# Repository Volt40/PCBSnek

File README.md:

# PCBSnek
PCB Business card with an integrated playable snake game.
Files are ready to be manufactured and assembled with JLCPCB.

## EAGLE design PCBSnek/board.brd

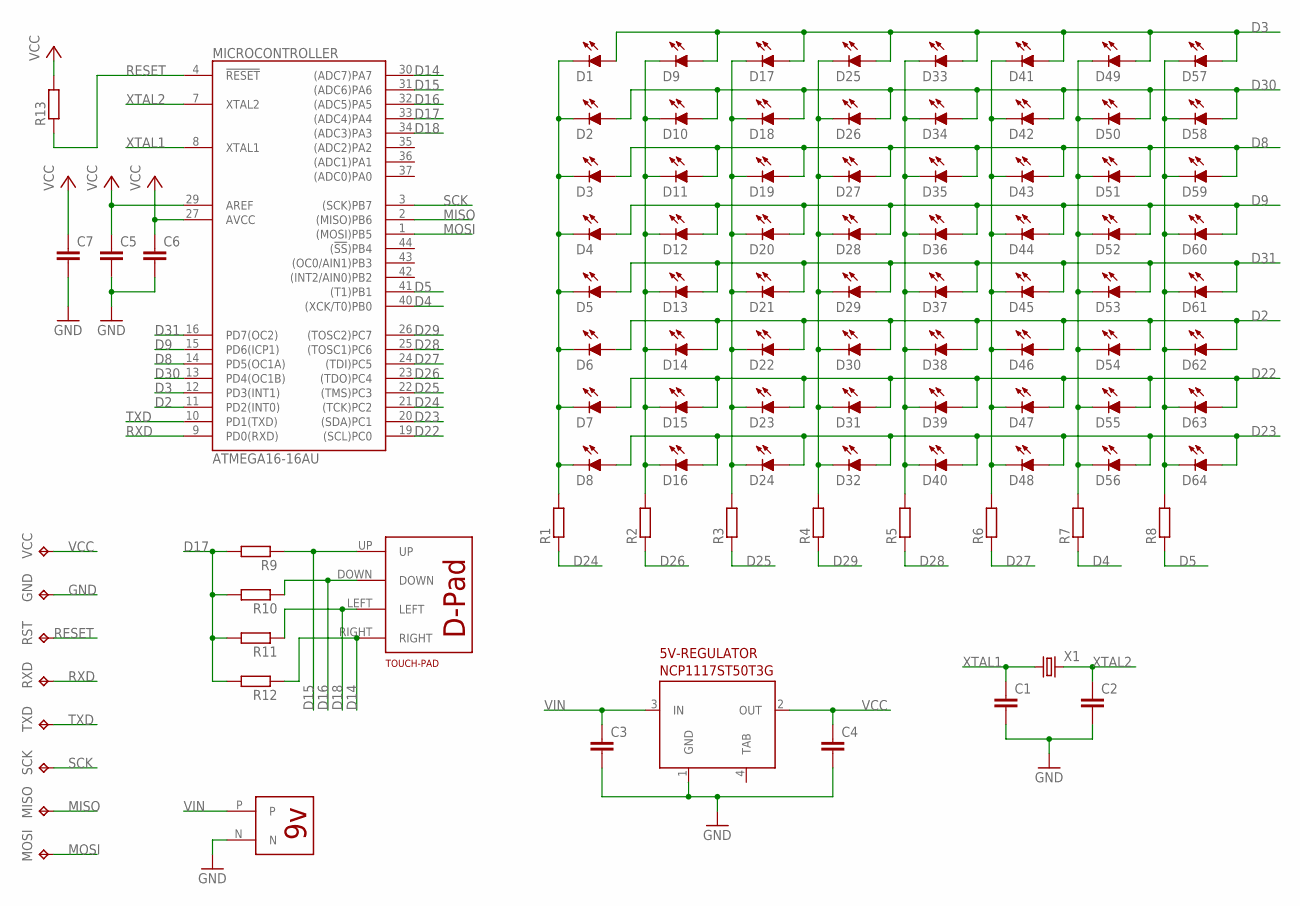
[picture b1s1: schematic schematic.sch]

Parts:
5V-REGULATOR: NCP1117ST50T3G; SOT223
C1, C2, C3, C4, C5, C6, C7: C-EUC0603; C0603
D1, D2, D3, D4, D5, D6, D7, D8, D9, D10, D11, D12, D13, D14, D15, D16, D17, D18, D19, D20, D21, D22, D23, D24, D25, D26, D27, D28, D29, D30, D31, D32, D33, D34, D35, D36, D37, D38, D39, D40, D41, D42, D43, D44, D45, D46, D47, D48, D49, D50, D51, D52, D53, D54, D55, D56, D57, D58, D59, D60, D61, D62, D63, D64: LED_LEDCHIP-LED0603MP; LED_CHIP-LED0603MP
GND: TPB2,54; B2,54
MICROCONTROLLER: ATMEGA16-16AU; QFP44_10X10_0.80
MISO: TPB2,54; B2,54
MOSI: TPB2,54; B2,54
R1, R2, R3, R4, R5, R6, R7, R8, R9, R10, R11, R12, R13: R-EU_R0603; R0603
RST: TPB2,54; B2,54
RXD: TPB2,54; B2,54
SCK: TPB2,54; B2,54
TOUCH-PAD: DPAD; D-PAD
TXD: TPB2,54; B2,54
U$1: BAT
VCC: TPB2,54; B2,54
X1: X322516MLB4SI; SMD3225

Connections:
D2: D6.A, D14.A, D22.A, D30.A, D38.A, D46.A, D54.A, D62.A, MICROCONTROLLER.11 (PD2(INT0))
D3: D1.A, D9.A, D17.A, D25.A, D33.A, D41.A, D49.A, D57.A, MICROCONTROLLER.12 (PD3(INT1))
D4: MICROCONTROLLER.40 ((XCK/T0)PB0), R7.1
D5: MICROCONTROLLER.41 ((T1)PB1), R8.1
D8: D3.A, D11.A, D19.A, D27.A, D35.A, D43.A, D51.A, D59.A, MICROCONTROLLER.14 (PD5(OC1A))
D9: D4.A, D12.A, D20.A, D28.A, D36.A, D44.A, D52.A, D60.A, MICROCONTROLLER.15 (PD6(ICP1))
D14: MICROCONTROLLER.30 ((ADC7)PA7), R12.1, TOUCH-PAD.RIGHT
D15: MICROCONTROLLER.31 ((ADC6)PA6), R9.1, TOUCH-PAD.UP
D16: MICROCONTROLLER.32 ((ADC5)PA5), R10.1, TOUCH-PAD.DOWN
D17: MICROCONTROLLER.33 ((ADC4)PA4), R9.2, R10.2, R11.2, R12.2
D18: MICROCONTROLLER.34 ((ADC3)PA3), R11.1, TOUCH-PAD.LEFT
D22: D7.A, D15.A, D23.A, D31.A, D39.A, D47.A, D55.A, D63.A, MICROCONTROLLER.19 ((SCL)PC0)
D23: D8.A, D16.A, D24.A, D32.A, D40.A, D48.A, D56.A, D64.A, MICROCONTROLLER.20 ((SDA)PC1)
D24: MICROCONTROLLER.21 ((TCK)PC2), R1.1
D25: MICROCONTROLLER.22 ((TMS)PC3), R3.1
D26: MICROCONTROLLER.23 ((TDO)PC4), R2.1
D27: MICROCONTROLLER.24 ((TDI)PC5), R6.1
D28: MICROCONTROLLER.25 ((TOSC1)PC6), R5.1
D29: MICROCONTROLLER.26 ((TOSC2)PC7), R4.1
D30: D2.A, D10.A, D18.A, D26.A, D34.A, D42.A, D50.A, D58.A, MICROCONTROLLER.13 (PD4(OC1B))
D31: D5.A, D13.A, D21.A, D29.A, D37.A, D45.A, D53.A, D61.A, MICROCONTROLLER.16 (PD7(OC2))
GND: 5V-REGULATOR.1 (GND), C1.2, C2.2, C3.2, C4.2, C5.2, C6.2, C7.2, GND.TP, MICROCONTROLLER.6 (GND), MICROCONTROLLER.18 (GND), MICROCONTROLLER.28 (GND), MICROCONTROLLER.39 (GND), U$1.N
MISO: MICROCONTROLLER.2 ((MISO)PB6), MISO.TP
MOSI: MICROCONTROLLER.1 ((MOSI)PB5), MOSI.TP
unnamed: D1.C, D2.C, D3.C, D4.C, D5.C, D6.C, D7.C, D8.C, R1.2
unnamed: D9.C, D10.C, D11.C, D12.C, D13.C, D14.C, D15.C, D16.C, R2.2
unnamed: D17.C, D18.C, D19.C, D20.C, D21.C, D22.C, D23.C, D24.C, R3.2
unnamed: D25.C, D26.C, D27.C, D28.C, D29.C, D30.C, D31.C, D32.C, R4.2
unnamed: D33.C, D34.C, D35.C, D36.C, D37.C, D38.C, D39.C, D40.C, R5.2
unnamed: D41.C, D42.C, D43.C, D44.C, D45.C, D46.C, D47.C, D48.C, R6.2
unnamed: D49.C, D50.C, D51.C, D52.C, D53.C, D54.C, D55.C, D56.C, R7.2
unnamed: D57.C, D58.C, D59.C, D60.C, D61.C, D62.C, D63.C, D64.C, R8.2
RESET: MICROCONTROLLER.4 (!RESET), R13.1, RST.TP
RXD: MICROCONTROLLER.9 (PD0(RXD)), RXD.TP
SCK: MICROCONTROLLER.3 ((SCK)PB7), SCK.TP
TXD: MICROCONTROLLER.10 (PD1(TXD)), TXD.TP
VCC: 5V-REGULATOR.2 (OUT), C4.1, C5.1, C6.1, C7.1, MICROCONTROLLER.5 (VCC), MICROCONTROLLER.17 (VCC), MICROCONTROLLER.27 (AVCC), MICROCONTROLLER.29 (AREF), MICROCONTROLLER.38 (VCC), R13.2, VCC.TP
VIN: 5V-REGULATOR.3 (IN), C3.1, U$1.P
XTAL1: C1.1, MICROCONTROLLER.8 (XTAL1), X1.1
XTAL2: C2.1, MICROCONTROLLER.7 (XTAL2), X1.3 (2)

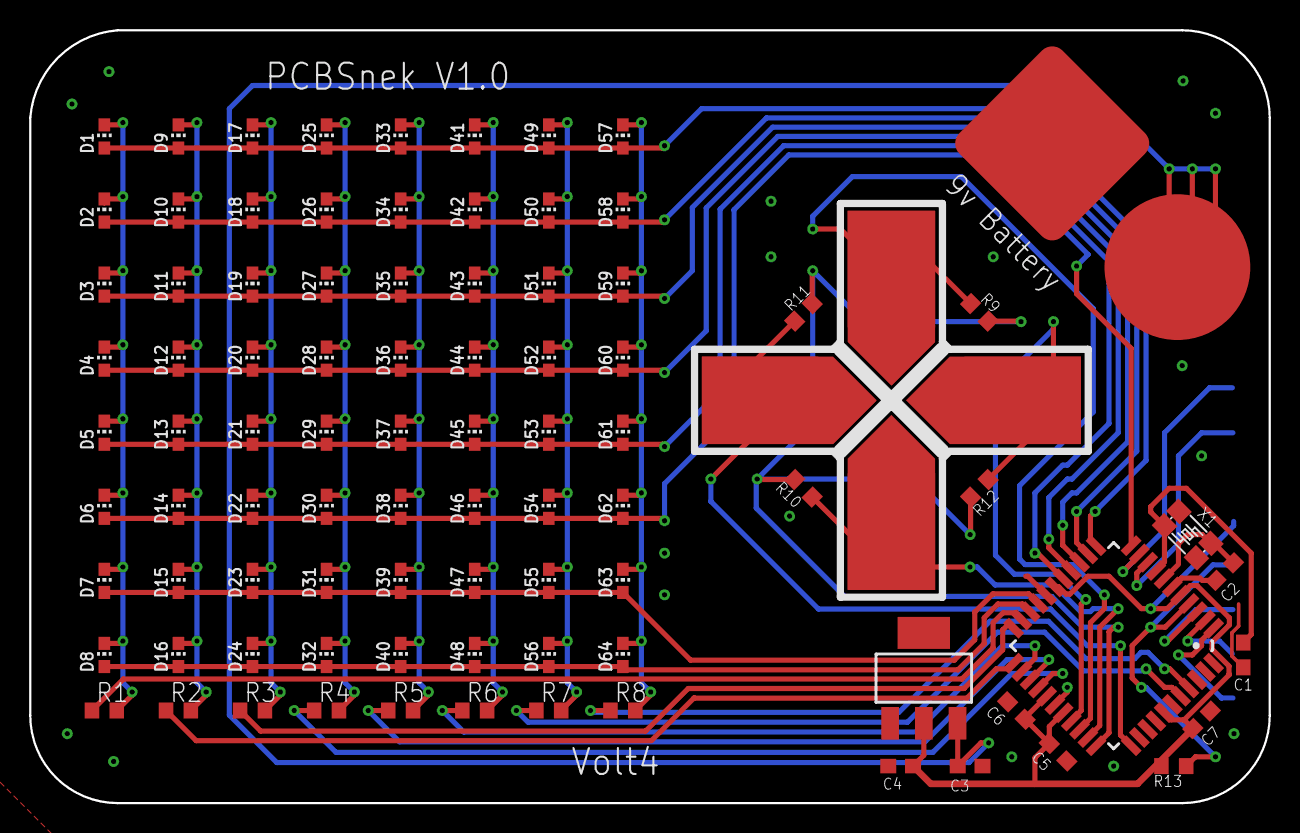
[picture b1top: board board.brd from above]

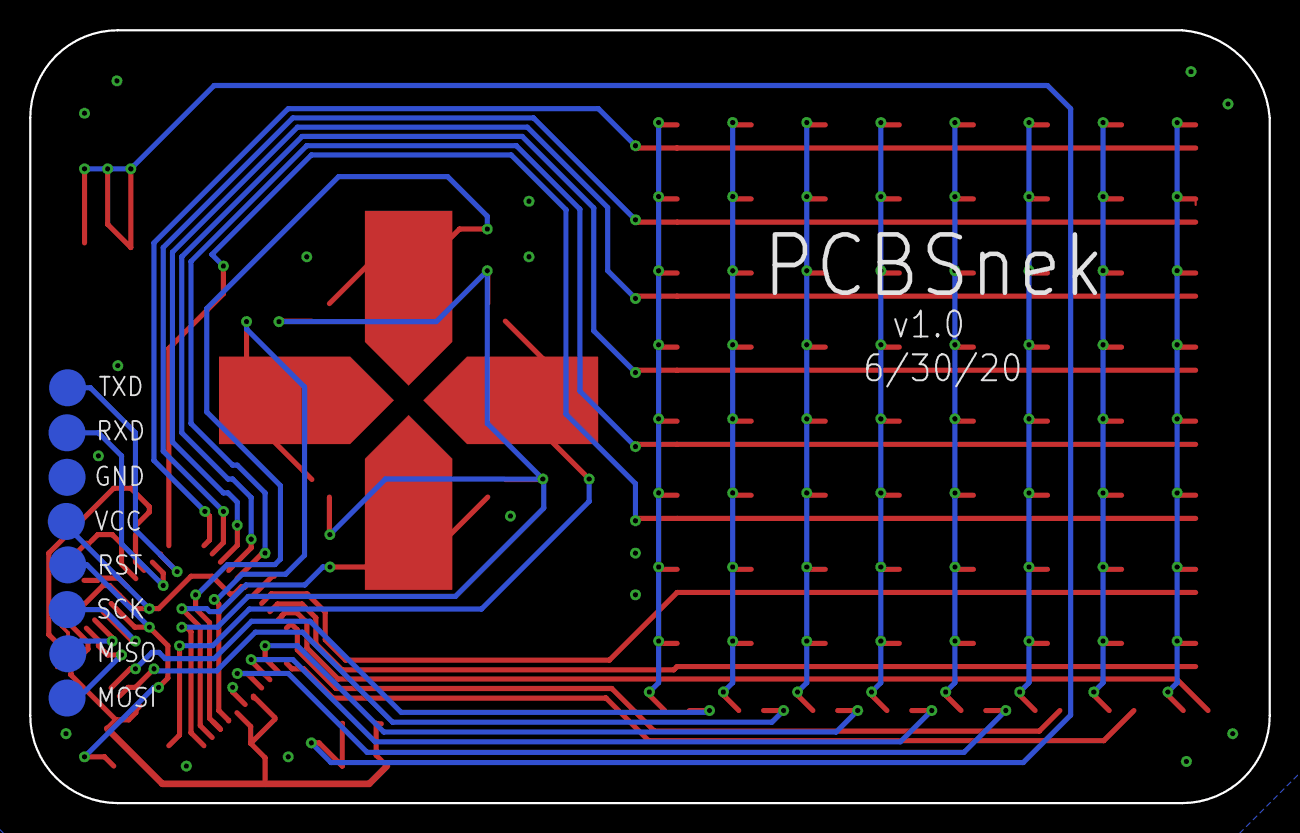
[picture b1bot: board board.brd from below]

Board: 2 copper layers, 85.0 x 53.0 mm, 97 parts (8 on the bottom side), 40 nets.

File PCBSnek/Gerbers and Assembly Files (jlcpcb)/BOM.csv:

Qty,Designator,Footprint,Comment,LCSC Part #,Description,,,,,,,
1,5V-REGULATOR,SOT-223,ncp1117 5v regulator,NCP1117ST50T3G,NCP1117 5V,,,,,,,
2,"C1, C2",C0603,22pf,CL10C220JB8NNNC,CAPACITOR,,,,,,,
1,C3,C0603,10uf,CL10A106KP8NNNC,CAPACITOR,,,,,,,
1,C4,C0603,1uf,CL10A105KB8NNNC,CAPACITOR,,,,,,,
3,"C5, C6, C7",C0603,100nf,CC0603KRX7R9BB104,CAPACITOR,,,,,,,
64,"D1, D2, D3, D4, D5, D6, D7, D8, D9, D10, D11, D12, D13, D14, D15, D16, D17, D18, D19, D20, D21, D22, D23, D24, D25, D26, D27, D28, D29, D30, D31, D32, D33, D34, D35, D36, D37, D38, D39, D40, D41, D42, D43, D44, D45, D46, D47, D48, D49, D50, D51, D52, D53, D54, D55, D56, D57, D58, D59, D60, D61, D62, D63, D64",0603,red led,KT-0603R,LED,,,,,,,
1,MICROCONTROLLER,QFP44_10X10_0.80,8-bit AVR Microcontroller,ATMEGA16A-AU,8-bit AVR Microcontroller,,,,,,,
9,"R1, R2, R3, R4, R5, R6, R7, R8, R13",R0603,10k,0603WAF1002T5E,RESISTOR,,,,,,,
4,"R9, R10, R11, R12",R0603,150k,0603WAF1503T5E,RESISTOR,,,,,,,
1,X1,SMD3225,16mhz,X322516MLB4SI,CRYSTAL,,,,,,,
,,,,,,,,,,,,
,,,,,,,,,,,,
,,,,,,,,,,,,
,,,,,,,,,,,,
,,,,,,,,,,,,
,,,,,,,,,,,,
,,,,,,,,,,,,
,,,,,,,,,,,,
,,,,,,,,,,,,
,,,,,,,,,,,,
,,,,,,,,,,,,
,,,,,,,,,,,,
,,,,,,,,,,,,
,,,,,,,,,,,,
,,,,,,,,,,,,
,,,,,,,,,,,,
,,,,,,,,,,,,
,,,,,,,,,,,,
,,,,,,,,,,,,
,,,,,,,,,,,,
,,,,,,,,,,,,
,,,,,,,,,,,,
,,,,,,,,,,,,
,,,,,,,,,,,,
,,,,,,,,,,,,
,,,,,,,,,,,,
,,,,,,,,,,,,
,,,,,,,,,,,,
,,,,,,,,,,,,
,,,,,,,,,,,,
,,,,,,,,,,,,
,,,,,,,,,,,,
,,,,,,,,,,,,
,,,,,,,,,,,,
,,,,,,,,,,,,
,,,,,,,,,,,,
,,,,,,,,,,,,
,,,,,,,,,,,,
,,,,,,,,,,,,
,,,,,,,,,,,,
,,,,,,,,,,,,
,,,,,,,,,,,,
,,,,,,,,,,,,
,,,,,,,,,,,,
,,,,,,,,,,,,
,,,,,,,,,,,,
,,,,,,,,,,,,
,,,,,,,,,,,,
,,,,,,,,,,,,
,,,,,,,,,,,,
,,,,,,,,,,,,
,,,,,,,,,,,,
,,,,,,,,,,,,
,,,,,,,,,,,,
,,,,,,,,,,,,
,,,,,,,,,,,,
,,,,,,,,,,,,
,,,,,,,,,,,,
,,,,,,,,,,,,
,,,,,,,,,,,,
,,,,,,,,,,,,
,,,,,,,,,,,,
,,,,,,,,,,,,
,,,,,,,,,,,,
,,,,,,,,,,,,
,,,,,,,,,,,,
,,,,,,,,,,,,
,,,,,,,,,,,,
,,,,,,,,,,,,
,,,,,,,,,,,,
,,,,,,,,,,,,
,,,,,,,,,,,,
,,,,,,,,,,,,
,,,,,,,,,,,,
,,,,,,,,,,,,
,,,,,,,,,,,,
,,,,,,,,,,,,
,,,,,,,,,,,,
,,,,,,,,,,,,
,,,,,,,,,,,,
,,,,,,,,,,,,
,,,,,,,,,,,,
,,,,,,,,,,,,
,,,,,,,,,,,,
,,,,,,,,,,,,
,,,,,,,,,,,,
,,,,,,,,,,,,None

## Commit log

2020-07-06 V1.0
